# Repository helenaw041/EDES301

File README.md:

# EDES301
Repository for EDES301 coursework

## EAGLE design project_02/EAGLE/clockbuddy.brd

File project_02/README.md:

# Digital Clock Buddy
A desk clock that tells you the time and date, temperature, and conditions outside. There will be a button that can toggle between the 4 US time zones with LED indicators. There is another button for the user to manually check the current time and conditions. The default will be every 15 seconds for time and date and on press for temperature and weather conditions. 
What each subfolder contains: 
- EAGLE: EAGLE files to library used, board, and schematic
- MFG: Gerber files
- docs: documentation

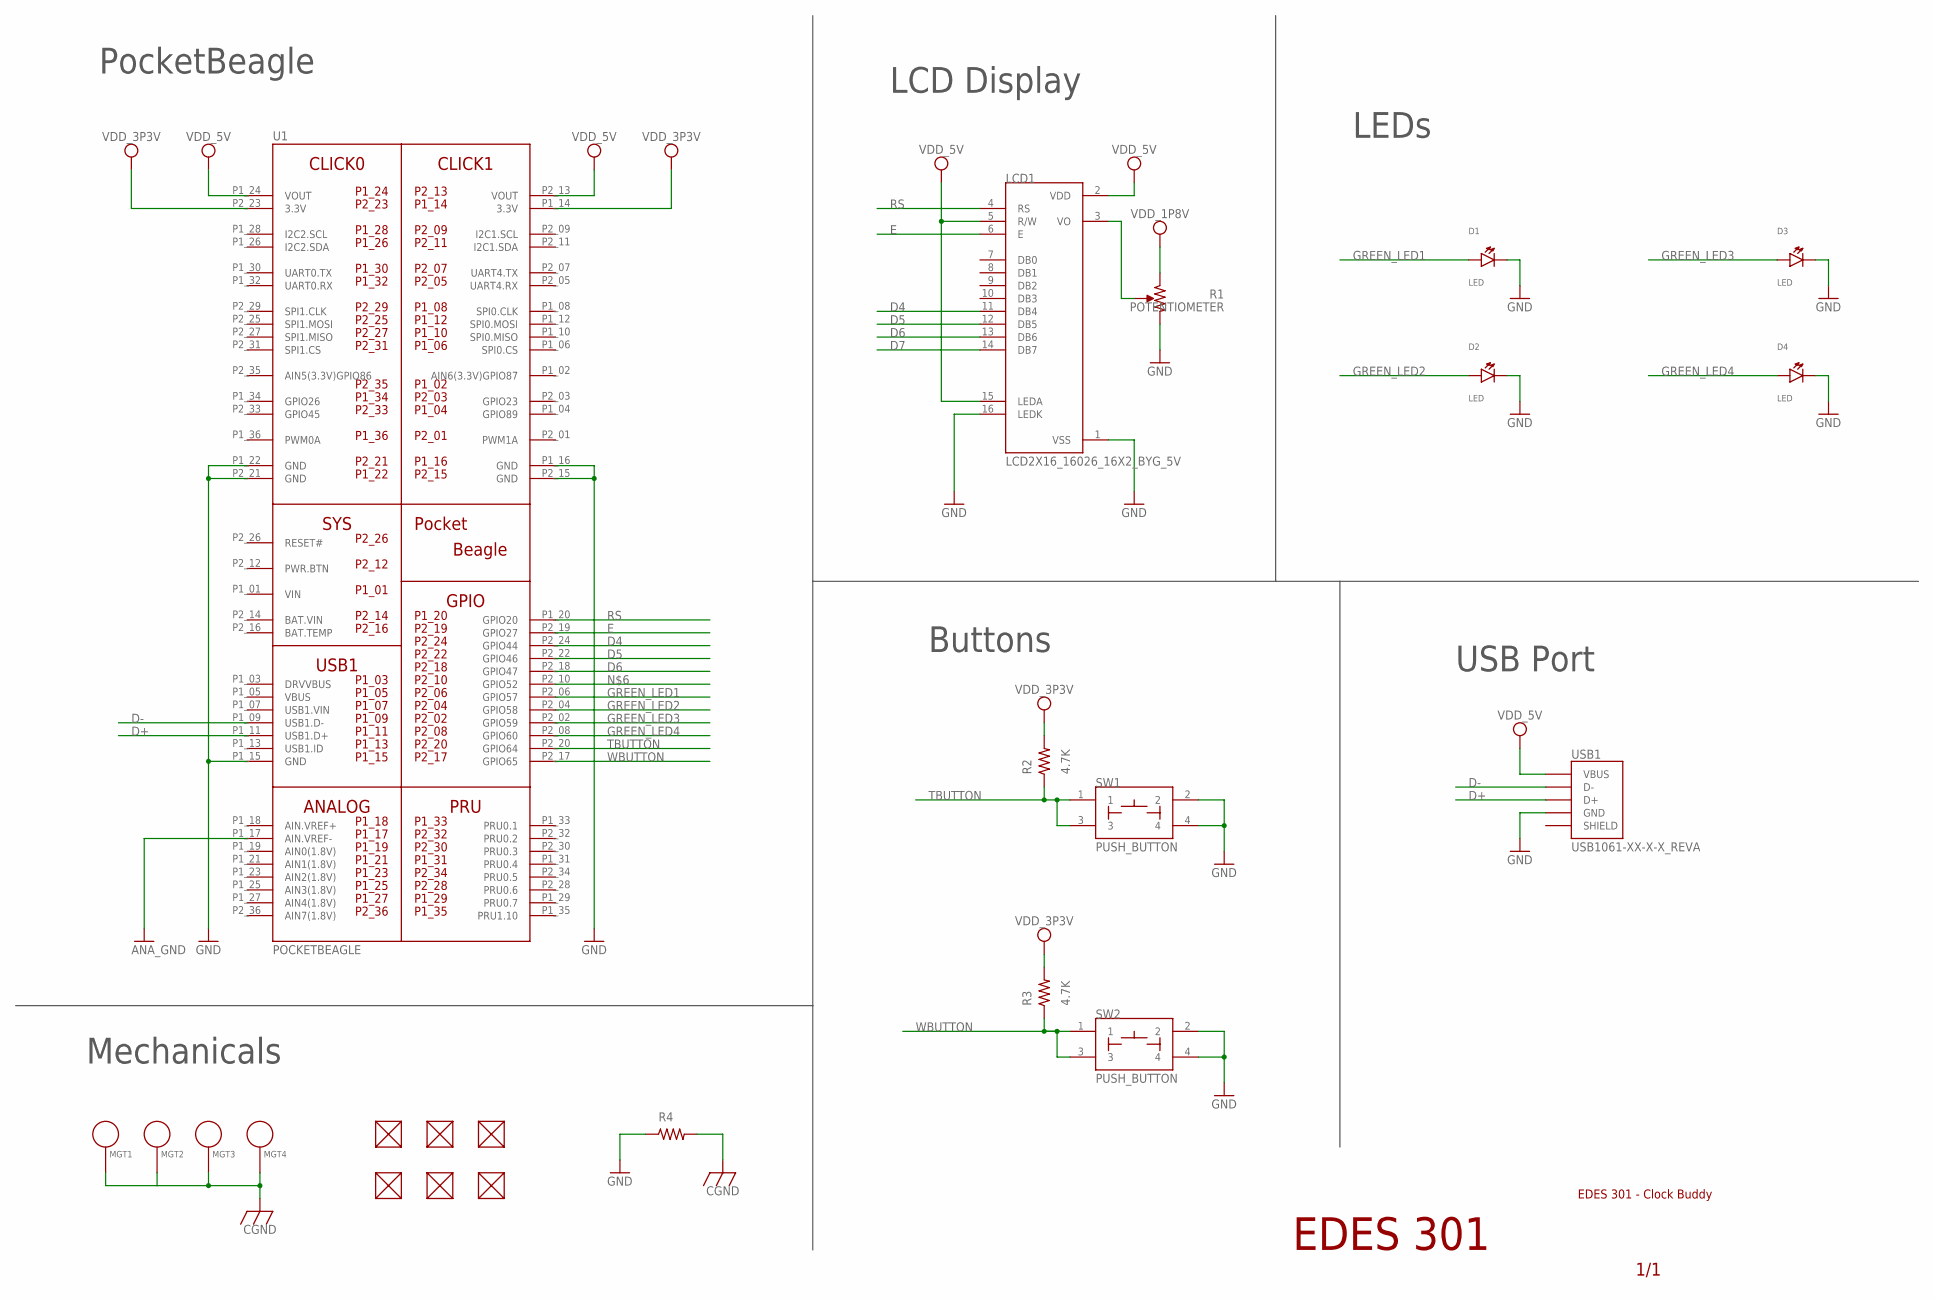
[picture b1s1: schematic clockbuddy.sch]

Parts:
D1, D2, D3, D4: LED; EIA-STD
FUD1, FUD2, FUD3, FUD4, FUD5, FUD6: FIDUCIAL; FIDUCIAL_40MIL
LCD1: LCD2X16_16026_16X2_BYG_5V; LCD_LCD2X16
MGT1, MGT2, MGT3, MGT4: MOUNTING_HOLE
R1: POTENTIOMETER; POT-PO90S
R2, R3: 4.7K; R0603
R4: R_R0805; R0805
SW1, SW2: PUSH_BUTTON; BUTTON_12.5MM
U1: POCKETBEAGLE
USB1: USB1061-XX-X-X_REVA; GCT_USB1061-XX-X-X_REVA

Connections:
ANA_GND: U1.P1_17 (AIN.VREF-)
BAT.VIN: U1.P2_14 (BAT.VIN)
CGND: MGT1.P$1, MGT2.P$1, MGT3.P$1, MGT4.P$1, R4.2
D4: LCD1.11 (DB4), U1.P2_24 (GPIO44)
D5: LCD1.12 (DB5), U1.P2_22 (GPIO46)
D6: LCD1.13 (DB6), U1.P2_18 (GPIO47)
D7: LCD1.14 (DB7)
D+: U1.P1_11 (USB1.D+), USB1.3 (D+)
D-: U1.P1_09 (USB1.D-), USB1.2 (D-)
E: LCD1.6 (E), U1.P2_19 (GPIO27)
GND: D1.CATHODE, D2.CATHODE, D3.CATHODE, D4.CATHODE, LCD1.1 (VSS), LCD1.16 (LEDK), R1.CW, R4.1, SW1.2, SW1.4, SW2.2, SW2.4, U1.P1_15 (GND), U1.P1_16 (GND), U1.P1_22 (GND), U1.P2_15 (GND), U1.P2_21 (GND), USB1.4 (GND)
GREEN_LED1: D1.ANODE, U1.P2_06 (GPIO57)
GREEN_LED2: D2.ANODE, U1.P2_04 (GPIO58)
GREEN_LED3: D3.ANODE, U1.P2_02 (GPIO59)
GREEN_LED4: D4.ANODE, U1.P2_08 (GPIO60)
unnamed: LCD1.3 (VO), R1.S
RS: LCD1.4 (RS), U1.P1_20 (GPIO20)
SHIELD: USB1.5 (SHIELD), USB1.6 (SHIELD)
TBUTTON: R2.1, SW1.1, SW1.3, U1.P2_20 (GPIO64)
VDD_1P8V: R1.CCW
VDD_3P3V: R2.2, R3.2, U1.P1_14 (3.3V), U1.P2_23 (3.3V)
VDD_5V: LCD1.2 (VDD), LCD1.5 (R/W), LCD1.15 (LEDA), U1.P1_24 (VOUT), U1.P2_13 (VOUT), USB1.1 (VBUS)
VIN: U1.P1_01 (VIN)
WBUTTON: R3.1, SW2.1, SW2.3, U1.P2_17 (GPIO65)

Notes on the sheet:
EDES 301
EDES 301 - Clock Buddy
1/1
PocketBeagle
LCD Display
LEDs
Buttons
Mechanicals
USB Port

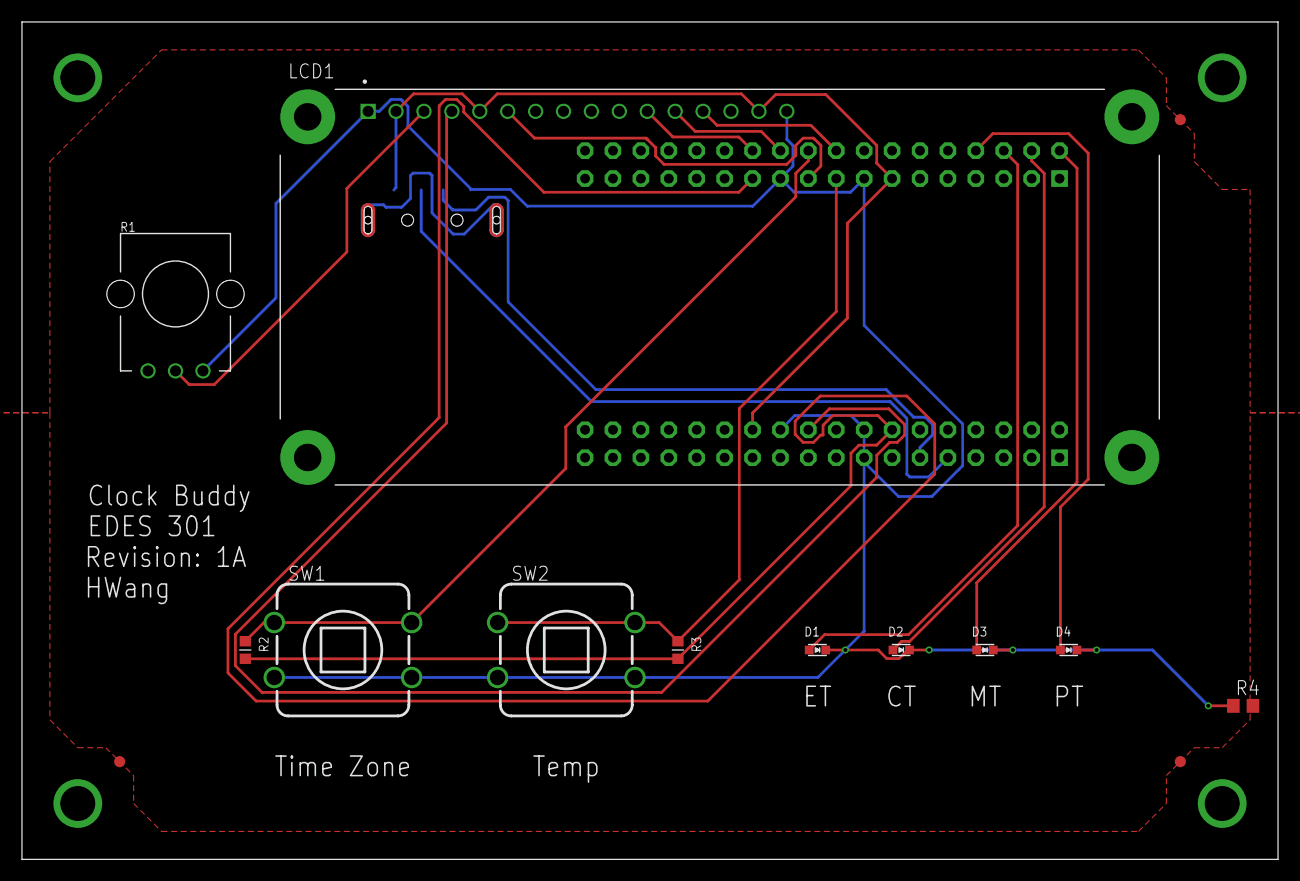
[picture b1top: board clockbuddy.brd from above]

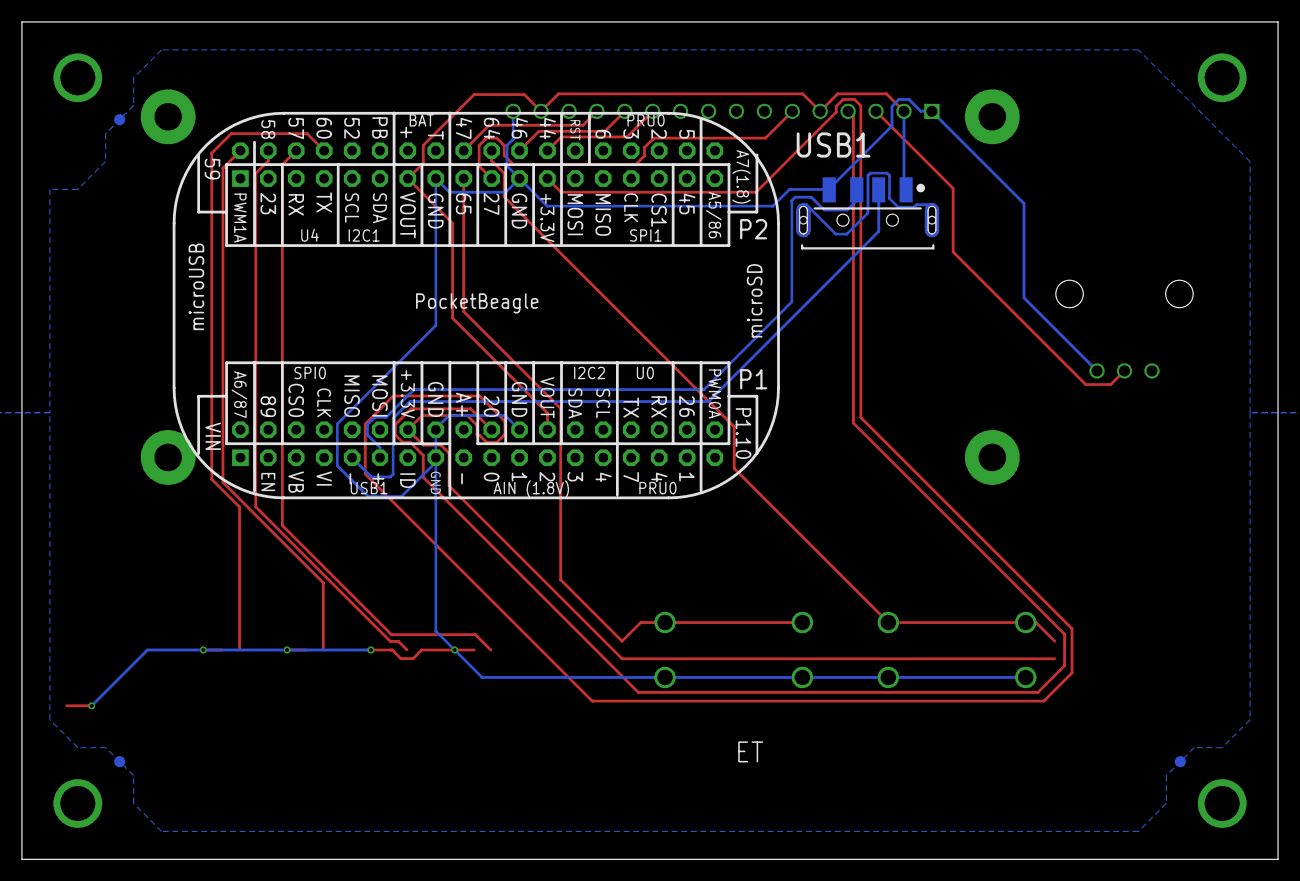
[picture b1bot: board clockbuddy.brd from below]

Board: 4 copper layers, 114.3 x 76.2 mm, 23 parts (5 on the bottom side), 19 nets.

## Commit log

2025-02-01 Updating README.md
2025-02-10 Create assignment_03
2025-02-15 simpelcalc
2025-02-16 simple_calc
2025-02-16 blink
2025-02-16 button
2025-02-23 Create adsf
2025-03-06 Updates or something
2025-03-06 IMportant change
2025-03-06 Potentiometer and Servo
2025-03-23 HowToPush
2025-04-21 project
2025-04-22 project display updates
2025-04-22 updated display
2025-04-23 Attempt to save
2025-04-26 final updates
2025-05-05 Create project_02
2025-05-05 Clockbuddy eagle files
2025-05-05 Create mfg
2025-05-05 Create docs
